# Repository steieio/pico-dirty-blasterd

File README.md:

# Pico Dirty Blasterd
USB Blaster adapters for [pico-dirtyJtag](https://github.com/phdussud/pico-dirtyJtag)

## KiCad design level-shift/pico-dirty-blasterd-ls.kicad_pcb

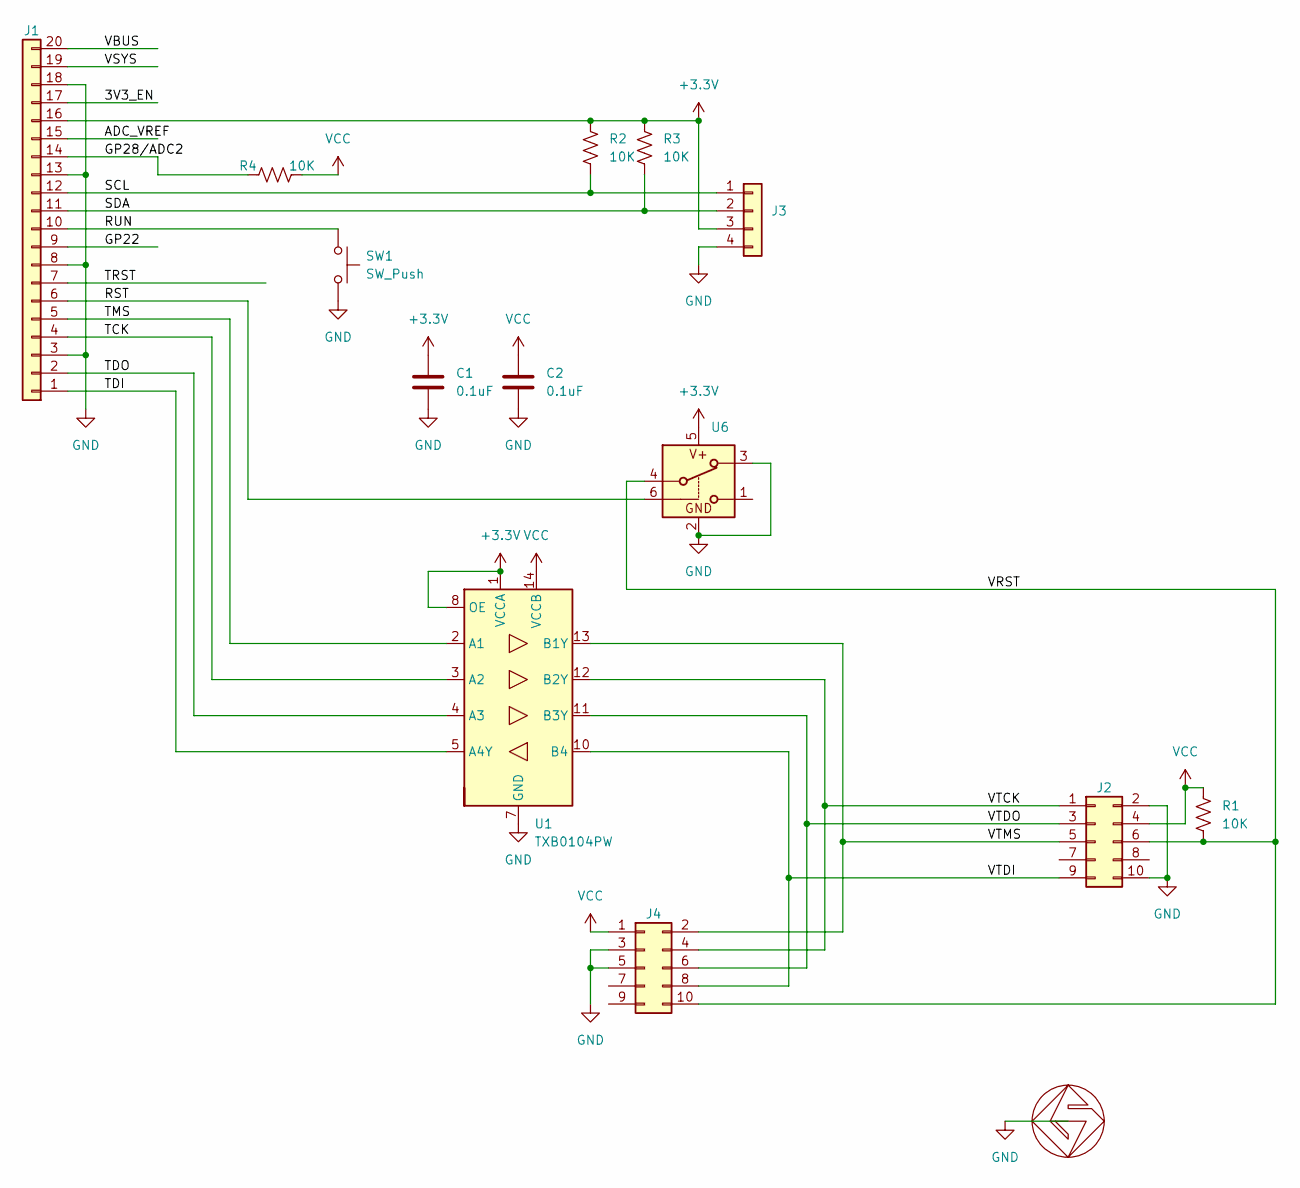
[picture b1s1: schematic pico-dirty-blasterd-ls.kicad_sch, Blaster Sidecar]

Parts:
C1, C2: 0.1uF; C_0603_1608Metric_Pad1.08x0.95mm_HandSolder
GS1: GS_logo; gs_logo_200mil
J1: Conn_01x20; Sidecar-20
J2: Conn_02x05_Odd_Even; BHR-10-VSG-SMT_2x05_P2.54mm_Vertical_SMD
J3: Conn_01x04; JST_SH_SM04B-SRSS-TB_1x04-1MP_P1.00mm_Horizontal
J4: Conn_02x05_Odd_Even; PinHeader_2x05_P1.27mm_Vertical_SMD
R1, R2, R3, R4: 10K; R_0603_1608Metric_Pad0.98x0.95mm_HandSolder
SW1: SW_Push; SW_Push_1P1T_NO_Vertical_Wuerth_434133025816
U1: TXB0104PW; TSSOP-14_4.4x5mm_P0.65mm
U6: TS5A63157DBV; SOT-23-6

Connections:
+3.3V: C1.1, J1.16, J3.3, R2.1, R3.1, U1.1 (VCCA), U1.8 (OE), U6.5
/3V3_EN: J1.17
/ADC_VREF: J1.15
/GP22: J1.9
/GP28/ADC2: J1.14, R4.1
/RST: J1.6, U6.6
/RUN: J1.10, SW1.1
/SCL: J1.12, J3.1, R2.2
/SDA: J1.11, J3.2, R3.2
/TCK: J1.4, U1.3 (A2)
/TDI: J1.1, U1.5 (A4Y)
/TDO: J1.2, U1.4 (A3)
/TMS: J1.5, U1.2 (A1)
/TRST: J1.7
/VBUS: J1.20
/VRST: J2.6, J4.10, R1.2, U6.4
/VSYS: J1.19
/VTCK: J2.1, J4.4, U1.12 (B2Y)
/VTDI: J2.9, J4.8, U1.10 (B4)
/VTDO: J2.3, J4.6, U1.11 (B3Y)
/VTMS: J2.5, J4.2, U1.13 (B1Y)
GND: C1.2, C2.2, GS1.1 (GS), J1.3, J1.8, J1.13, J1.18, J2.2, J2.10, J3.4, J4.3, J4.5, SW1.2, U1.7 (GND), U6.2, U6.3
VCC: C2.1, J2.4, J4.1, R1.1, R4.2, U1.14 (VCCB)

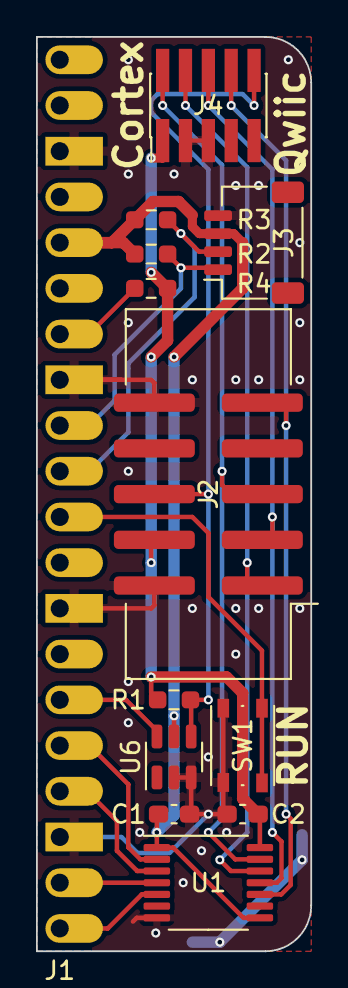
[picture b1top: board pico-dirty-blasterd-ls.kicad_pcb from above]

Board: 2 copper layers, 15.2 x 50.8 mm, 14 parts (1 on the bottom side), 17 nets.

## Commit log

2024-04-27 adding three boards
2024-04-28 adding docs
2024-04-29 additional documentation with pictures
2024-04-29 fixed indent
2024-04-30 fixed path to image in readme
